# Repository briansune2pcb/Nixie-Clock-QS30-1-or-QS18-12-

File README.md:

# Nixie-Clock-QS30-1-or-QS18-12-

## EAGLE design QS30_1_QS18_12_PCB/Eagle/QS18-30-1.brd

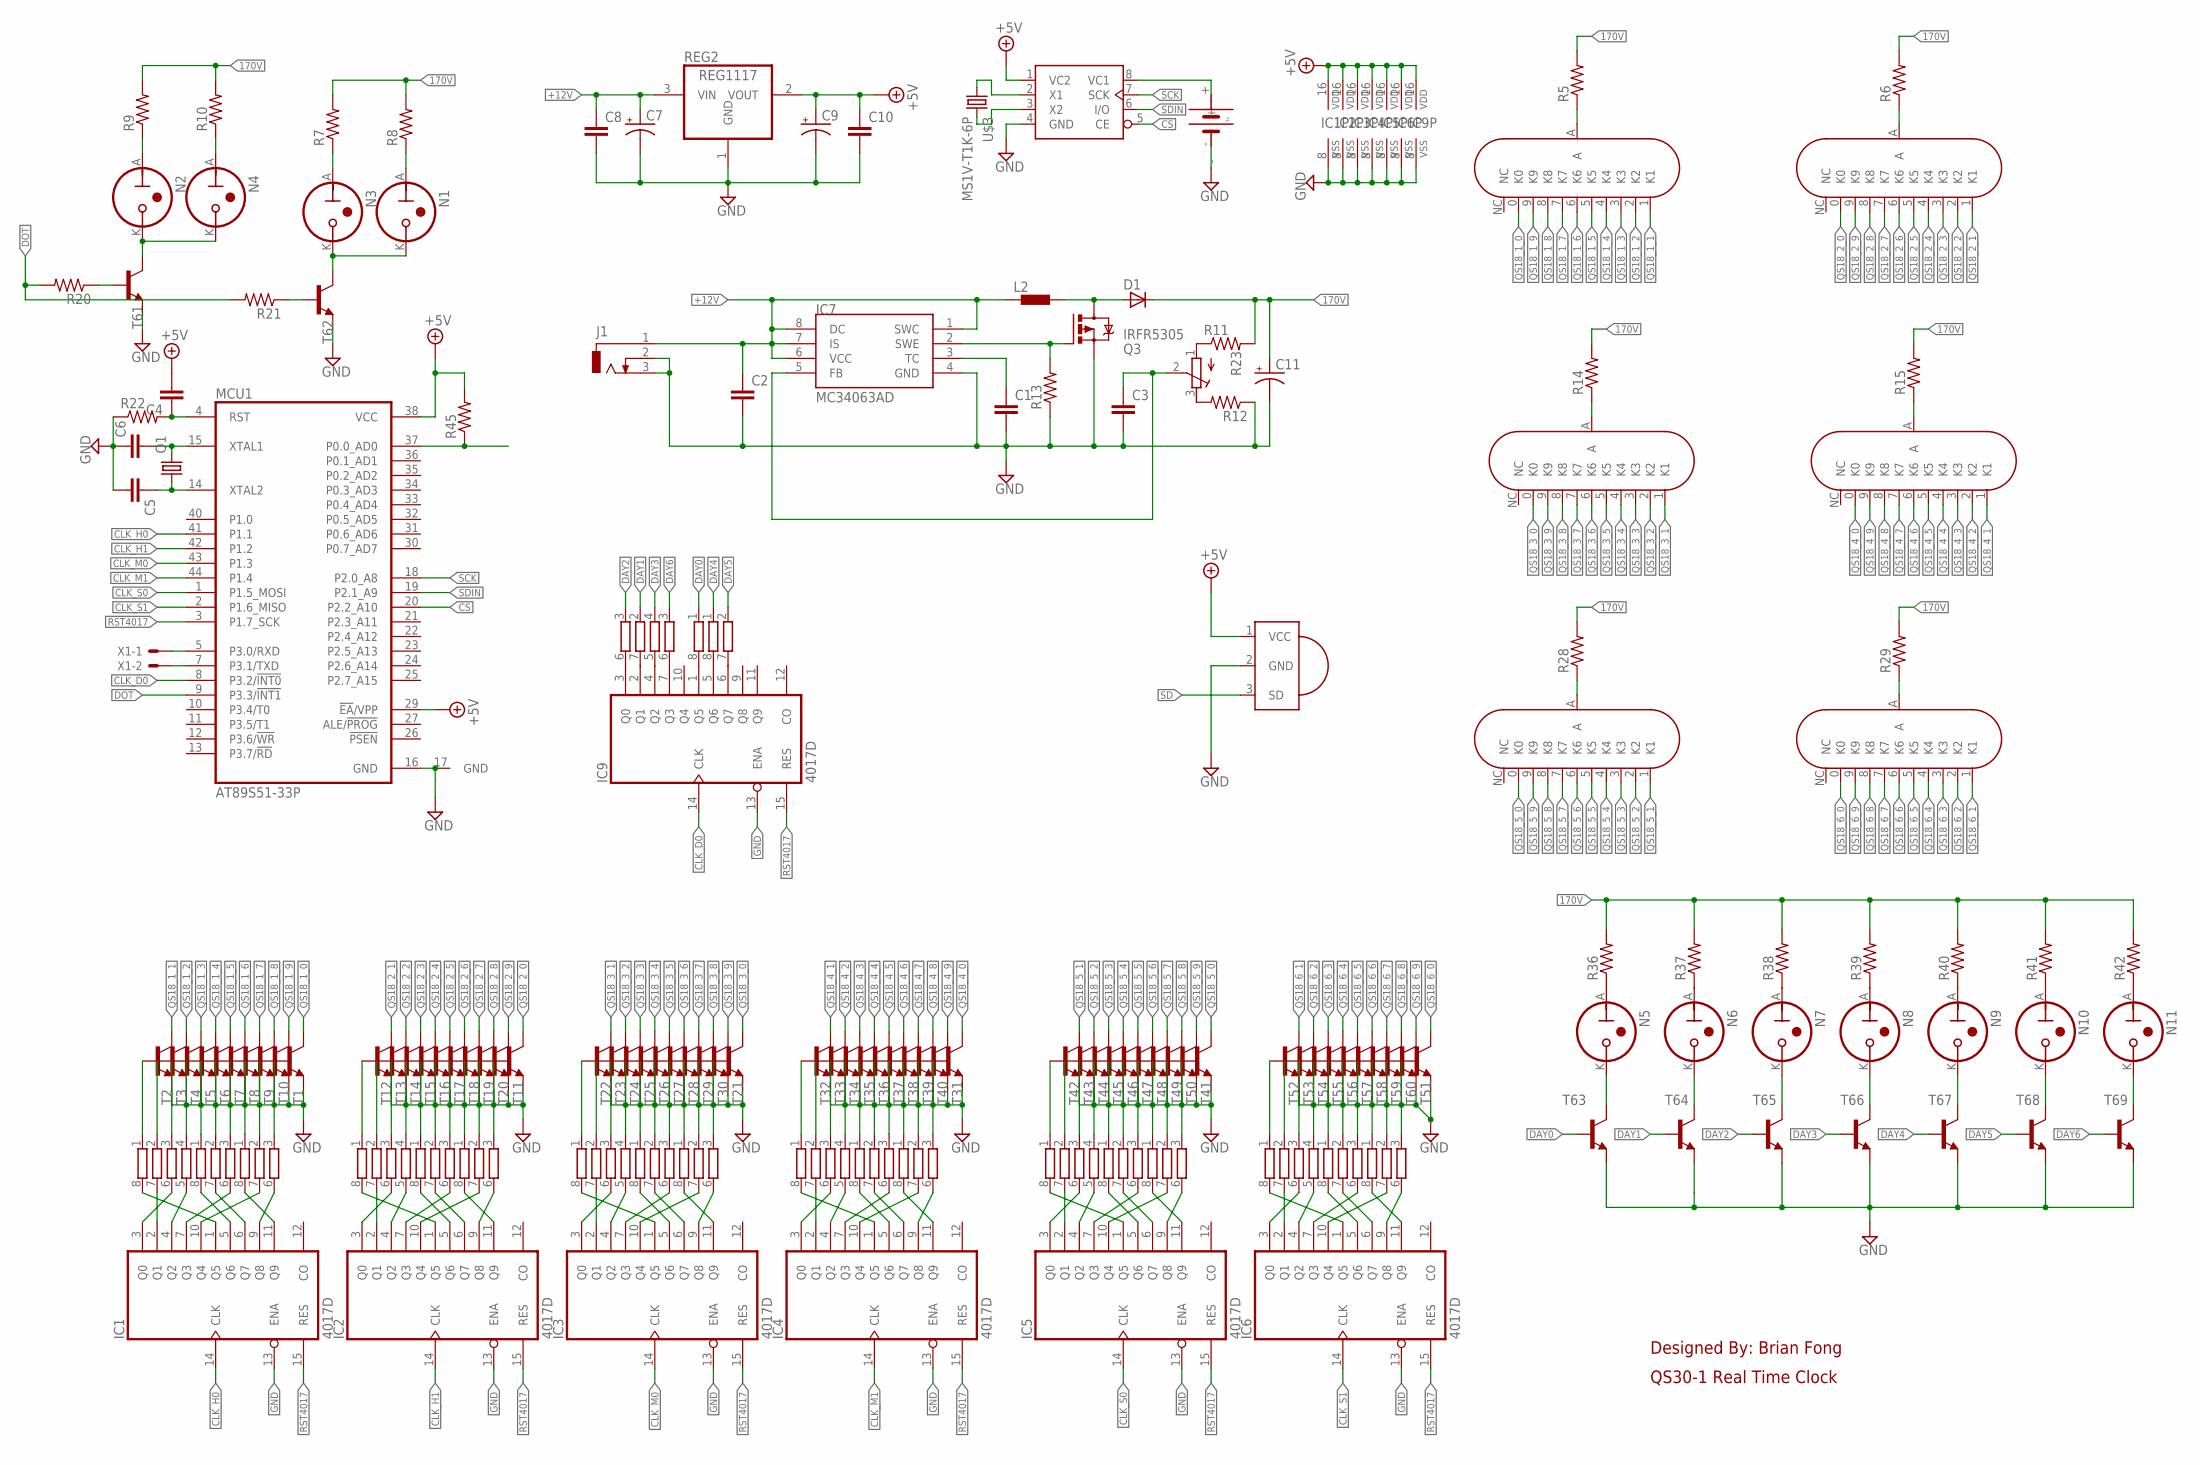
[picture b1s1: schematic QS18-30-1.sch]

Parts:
C1, C2, C3, C5, C6, C8, C10: C-EUC0805; C0805
C4: C-EUC1206; C1206
C7, C9: CPOL-USB/3528-21R; B/3528-21R
C11: CPOL-USG; PANASONIC_G
D1: D-SMB; SMB
IC1, IC2, IC3, IC4, IC5, IC6, IC9: 4017D; SO16
IC7: MC34063AD; SOIC8
J1: DCJ0303
L2: DR10301033; DR1033
MCU1: AT89S51-33P; TQFP44
N1, N2, N3, N4, N5, N6, N7, N8, N9, N10: IN-3
N11: Mon; IN-3
Q1: CRYSTALHC49UP; HC49UP
Q3: IRFR5305; D-PAK_TO252AA
R1, R2, R3, R4, R16, R17, R18, R19, R24, R25, R26, R27, R30, R31, R32, R33, R34, R35, R43, R44: 4R-NEXB38V; EXB38V
R5, R6, R7, R8, R9, R10, R14, R15, R20, R21, R22, R28, R29, R36, R37, R38, R39, R40, R41, R42, R45: R-US_M0805; M0805
R11, R12, R13: R-US_R0805; R0805
R23: R-TRIMM3374; RTRIM3374
REG2: REG1117; SOT223
T1, T2, T3, T4, T5, T6, T7, T8, T9, T10, T11, T12, T13, T14, T15, T16, T17, T18, T19, T20, T21, T22, T23, T24, T25, T26, T27, T28, T29, T30, T31, T32, T33, T34, T35, T36, T37, T38, T39, T40, T41, T42, T43, T44, T45, T46, T47, T48, T49, T50, T51, T52, T53, T54, T55, T56, T57, T58, T59, T60, T61, T62, T63, T64, T65, T66, T67, T68, T69: MMBT5551LT1-NPN-SOT23-BEC; SOT23-BEC
TUBE1, TUBE2, TUBE3, TUBE4, TUBE5, TUBE6: QS30-1R1; QS30-1_V3
U$1: DS1302SOP08; SOP08
U$2: 1220BATTERY_SF; 1220BATTERY
U$3: MS1V-T1K-6P; MS1V-T1K
U$4: HX1838; TO92-
X1: 332-02

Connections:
170V: C11.+, D1.1 (C), R5.2, R6.2, R7.2, R8.2, R9.2, R10.2, R11.2, R14.2, R15.2, R28.2, R29.2, R36.2, R37.2, R38.2, R39.2, R40.2, R41.2, R42.2
+5V: C4.2, C9.+, C10.1, IC1.16 (VDD), IC2.16 (VDD), IC3.16 (VDD), IC4.16 (VDD), IC5.16 (VDD), IC6.16 (VDD), IC9.16 (VDD), MCU1.29 (!EA!/VPP), MCU1.38 (VCC), R45.2, REG2.2 (VOUT), U$1.1 (VC2), U$4.1 (VCC)
+12V: C2.1, C7.+, C8.1, IC7.1 (SWC), IC7.6 (VCC), IC7.7 (IS), IC7.8 (DC), J1.1, L2.1, REG2.3 (VIN)
CLK_D0: IC9.14 (CLK), MCU1.8 (P3.2/!INT0)
CLK_H0: IC1.14 (CLK), MCU1.41 (P1.1)
CLK_H1: IC2.14 (CLK), MCU1.42 (P1.2)
CLK_M0: IC3.14 (CLK), MCU1.43 (P1.3)
CLK_M1: IC4.14 (CLK), MCU1.44 (P1.4)
CLK_S0: IC5.14 (CLK), MCU1.1 (P1.5_MOSI)
CLK_S1: IC6.14 (CLK), MCU1.2 (P1.6_MISO)
CS: MCU1.20 (P2.2_A10), U$1.5 (CE)
DAY0: R43.1, T63.B
DAY1: R43.2 (1), T64.B
DAY2: R43.3 (1), T65.B
DAY3: R43.4 (1), T66.B
DAY4: R44.1, T67.B
DAY5: R44.2 (1), T68.B
DAY6: R44.3 (1), T69.B
DOT: MCU1.9 (P3.3/!INT1), R20.2, R21.2
GND: C1.2, C2.2, C3.2, C5.2, C6.1, C7.-, C8.2, C9.-, C10.2, C11.-, IC1.8 (VSS), IC1.13 (ENA), IC2.8 (VSS), IC2.13 (ENA), IC3.8 (VSS), IC3.13 (ENA), IC4.8 (VSS), IC4.13 (ENA), IC5.8 (VSS), IC5.13 (ENA), IC6.8 (VSS), IC6.13 (ENA), IC7.4 (GND), IC9.8 (VSS), IC9.13 (ENA), J1.2, J1.3, MCU1.16 (GND), MCU1.17 (GND), Q3.3 (S), R12.1, R13.1, R22.1, REG2.1 (GND), T1.E, T2.E, T3.E, T4.E, T5.E, T6.E, T7.E, T8.E, T9.E, T10.E, T11.E, T12.E, T13.E, T14.E, T15.E, T16.E, T17.E, T18.E, T19.E, T20.E, T21.E, T22.E, T23.E, T24.E, T25.E, T26.E, T27.E, T28.E, T29.E, T30.E, T31.E, T32.E, T33.E, T34.E, T35.E, T36.E, T37.E, T38.E, T39.E, T40.E, T41.E, T42.E, T43.E, T44.E, T45.E, T46.E, T47.E, T48.E, T49.E, T50.E, T51.E, T52.E, T53.E, T54.E, T55.E, T56.E, T57.E, T58.E, T59.E, T60.E, T61.E, T62.E, T63.E, T64.E, T65.E, T66.E, T67.E, T68.E, T69.E, U$1.4 (GND), U$2.-, U$4.2 (GND)
unnamed: C5.1, MCU1.14 (XTAL2), Q1.1
unnamed: C6.2, MCU1.15 (XTAL1), Q1.2
unnamed: R1.1, T2.B
unnamed: R1.2 (1), T3.B
unnamed: R1.3 (1), T4.B
unnamed: R4.1, T12.B
unnamed: R1.4 (1), T5.B
unnamed: R2.1, T6.B
unnamed: R2.2 (1), T7.B
unnamed: R2.3 (1), T8.B
unnamed: R3.1, T9.B
unnamed: R3.2 (1), T10.B
unnamed: R3.3 (1), T1.B
unnamed: R4.2 (1), T13.B
unnamed: R4.3 (1), T14.B
unnamed: R4.4 (1), T15.B
unnamed: R16.1, T16.B
unnamed: R16.2 (1), T17.B
unnamed: R16.3 (1), T18.B
unnamed: R17.1, T19.B
unnamed: R17.2 (1), T20.B
unnamed: R17.3 (1), T11.B
unnamed: R14.1, TUBE3.A
unnamed: R15.1, TUBE4.A
unnamed: R5.1, TUBE1.A
unnamed: R18.1, T22.B
unnamed: R6.1, TUBE2.A
unnamed: R18.2 (1), T23.B
unnamed: R18.3 (1), T24.B
unnamed: R18.4 (1), T25.B
unnamed: R19.1, T26.B
unnamed: R19.2 (1), T27.B
unnamed: R19.3 (1), T28.B
unnamed: R24.1, T29.B
unnamed: R24.2 (1), T30.B
unnamed: R24.3 (1), T21.B
unnamed: R25.1, T32.B
unnamed: R25.2 (1), T33.B
unnamed: R25.3 (1), T34.B
unnamed: R25.4 (1), T35.B
unnamed: R26.1, T36.B
unnamed: R26.2 (1), T37.B
unnamed: R26.3 (1), T38.B
unnamed: R27.1, T39.B
unnamed: R27.2 (1), T40.B
unnamed: R27.3 (1), T31.B
unnamed: IC3.1 (Q5), R18.8 (2)
unnamed: IC3.2 (Q1), R18.7 (2)
unnamed: N3.A, R7.1
unnamed: N1.A, R8.1
unnamed: N2.A, R9.1
unnamed: N4.A, R10.1
unnamed: IC7.2 (SWE), Q3.1 (G), R13.2
unnamed: MCU1.5 (P3.0/RXD), X1.1
unnamed: C1.1, IC7.3 (TC)
unnamed: C3.1, IC7.5 (FB), R23.2 (S)
unnamed: D1.2 (A), L2.2, Q3.4 (D)
unnamed: IC3.3 (Q0), R18.6 (2)
unnamed: IC3.4 (Q2), R18.5 (2)
unnamed: IC3.5 (Q6), R19.8 (2)
unnamed: MCU1.7 (P3.1/TXD), X1.2
unnamed: IC3.6 (Q7), R19.7 (2)
unnamed: IC3.7 (Q3), R19.6 (2)
unnamed: IC3.9 (Q8), R24.6 (2)
unnamed: IC3.11 (Q9), R24.8 (2)
unnamed: IC3.10 (Q4), R24.7 (2)
unnamed: IC4.3 (Q0), R25.6 (2)
unnamed: IC4.1 (Q5), R25.8 (2)
unnamed: IC4.2 (Q1), R25.7 (2)
unnamed: IC4.11 (Q9), R27.8 (2)
unnamed: IC4.9 (Q8), R27.6 (2)
unnamed: IC4.10 (Q4), R27.7 (2)
unnamed: IC4.4 (Q2), R25.5 (2)
unnamed: IC4.5 (Q6), R26.8 (2)
unnamed: IC4.6 (Q7), R26.7 (2)
unnamed: IC4.7 (Q3), R26.6 (2)
unnamed: IC1.1 (Q5), R1.8 (2)
unnamed: IC1.2 (Q1), R1.7 (2)
unnamed: IC1.3 (Q0), R1.6 (2)
unnamed: IC1.4 (Q2), R1.5 (2)
unnamed: IC1.5 (Q6), R2.8 (2)
unnamed: IC1.6 (Q7), R2.7 (2)
unnamed: IC1.7 (Q3), R2.6 (2)
unnamed: IC1.11 (Q9), R3.8 (2)
unnamed: IC1.10 (Q4), R3.7 (2)
unnamed: R28.1, TUBE5.A
unnamed: IC1.9 (Q8), R3.6 (2)
unnamed: R29.1, TUBE6.A
unnamed: N2.K, N4.K, T61.C
unnamed: R20.1, T61.B
unnamed: N1.K, N3.K, T62.C
unnamed: R21.1, T62.B
unnamed: IC2.1 (Q5), R4.8 (2)
unnamed: IC2.2 (Q1), R4.7 (2)
unnamed: IC2.3 (Q0), R4.6 (2)
unnamed: IC2.4 (Q2), R4.5 (2)
unnamed: IC2.5 (Q6), R16.8 (2)
unnamed: U$1.8 (VC1), U$2.+
unnamed: IC2.6 (Q7), R16.7 (2)
unnamed: IC2.7 (Q3), R16.6 (2)
unnamed: IC2.11 (Q9), R17.8 (2)
unnamed: IC2.10 (Q4), R17.7 (2)
unnamed: U$1.2 (X1), U$3.P$1 (1)
unnamed: C4.1, MCU1.4 (RST), R22.2
unnamed: U$1.3 (X2), U$3.P$2 (2)
unnamed: IC2.9 (Q8), R17.6 (2)
unnamed: R30.1, T42.B
unnamed: R30.2 (1), T43.B
unnamed: R30.3 (1), T44.B
unnamed: R30.4 (1), T45.B
unnamed: R31.1, T46.B
unnamed: R31.2 (1), T47.B
unnamed: R31.3 (1), T48.B
unnamed: R32.1, T49.B
unnamed: R32.2 (1), T50.B
unnamed: R32.3 (1), T41.B
unnamed: R33.1, T52.B
unnamed: R33.2 (1), T53.B
unnamed: R33.3 (1), T54.B
unnamed: R33.4 (1), T55.B
unnamed: R34.1, T56.B
unnamed: R34.2 (1), T57.B
unnamed: R34.3 (1), T58.B
unnamed: R35.1, T59.B
unnamed: R35.2 (1), T60.B
unnamed: R35.3 (1), T51.B
unnamed: IC5.1 (Q5), R30.8 (2)
unnamed: IC5.2 (Q1), R30.7 (2)
unnamed: IC5.3 (Q0), R30.6 (2)
unnamed: IC5.4 (Q2), R30.5 (2)
unnamed: IC5.5 (Q6), R31.8 (2)
unnamed: IC5.6 (Q7), R31.7 (2)
unnamed: IC5.7 (Q3), R31.6 (2)
unnamed: IC5.9 (Q8), R32.6 (2)
unnamed: IC5.11 (Q9), R32.8 (2)
unnamed: IC5.10 (Q4), R32.7 (2)
unnamed: IC6.3 (Q0), R33.6 (2)
unnamed: IC6.1 (Q5), R33.8 (2)
unnamed: IC6.2 (Q1), R33.7 (2)
unnamed: IC6.11 (Q9), R35.8 (2)
unnamed: IC6.9 (Q8), R35.6 (2)
unnamed: IC6.10 (Q4), R35.7 (2)
unnamed: IC6.4 (Q2), R33.5 (2)
unnamed: IC6.5 (Q6), R34.8 (2)
unnamed: IC6.6 (Q7), R34.7 (2)
unnamed: IC6.7 (Q3), R34.6 (2)
unnamed: N5.K, T63.C
unnamed: N6.K, T64.C
unnamed: N7.K, T65.C
unnamed: N8.K, T66.C
unnamed: N9.K, T67.C
unnamed: N10.K, T68.C
unnamed: N11.K, T69.C
unnamed: N5.A, R36.1
unnamed: N6.A, R37.1
unnamed: N8.A, R39.1
unnamed: N11.A, R42.1
unnamed: N10.A, R41.1
unnamed: N9.A, R40.1
unnamed: N7.A, R38.1
unnamed: R11.1, R23.1 (E)
unnamed: R12.2, R23.3 (A)
unnamed: IC9.1 (Q5), R43.8 (2)
unnamed: IC9.2 (Q1), R43.7 (2)
unnamed: IC9.3 (Q0), R43.6 (2)
unnamed: IC9.4 (Q2), R43.5 (2)
unnamed: IC9.7 (Q3), R44.6 (2)
unnamed: IC9.5 (Q6), R44.8 (2)
unnamed: IC9.6 (Q7), R44.7 (2)
QS18_1_0: T1.C, TUBE1.0 (K0)
QS18_1_1: T2.C, TUBE1.1 (K1)
QS18_1_2: T3.C, TUBE1.2 (K2)
QS18_1_3: T4.C, TUBE1.3 (K3)
QS18_1_4: T5.C, TUBE1.4 (K4)
QS18_1_5: T6.C, TUBE1.5 (K5)
QS18_1_6: T7.C, TUBE1.6 (K6)
QS18_1_7: T8.C, TUBE1.7 (K7)
QS18_1_8: T9.C, TUBE1.8 (K8)
QS18_1_9: T10.C, TUBE1.9 (K9)
QS18_2_0: T11.C, TUBE2.0 (K0)
QS18_2_1: T12.C, TUBE2.1 (K1)
QS18_2_2: T13.C, TUBE2.2 (K2)
QS18_2_3: T14.C, TUBE2.3 (K3)
QS18_2_4: T15.C, TUBE2.4 (K4)
QS18_2_5: T16.C, TUBE2.5 (K5)
QS18_2_6: T17.C, TUBE2.6 (K6)
QS18_2_7: T18.C, TUBE2.7 (K7)
QS18_2_8: T19.C, TUBE2.8 (K8)
QS18_2_9: T20.C, TUBE2.9 (K9)
QS18_3_0: T21.C, TUBE3.0 (K0)
QS18_3_1: T22.C, TUBE3.1 (K1)
QS18_3_2: T23.C, TUBE3.2 (K2)
QS18_3_3: T24.C, TUBE3.3 (K3)
QS18_3_4: T25.C, TUBE3.4 (K4)
QS18_3_5: T26.C, TUBE3.5 (K5)
QS18_3_6: T27.C, TUBE3.6 (K6)
QS18_3_7: T28.C, TUBE3.7 (K7)
QS18_3_8: T29.C, TUBE3.8 (K8)
QS18_3_9: T30.C, TUBE3.9 (K9)
QS18_4_0: T31.C, TUBE4.0 (K0)
QS18_4_1: T32.C, TUBE4.1 (K1)
QS18_4_2: T33.C, TUBE4.2 (K2)
QS18_4_3: T34.C, TUBE4.3 (K3)
QS18_4_4: T35.C, TUBE4.4 (K4)
QS18_4_5: T36.C, TUBE4.5 (K5)
QS18_4_6: T37.C, TUBE4.6 (K6)
QS18_4_7: T38.C, TUBE4.7 (K7)
QS18_4_8: T39.C, TUBE4.8 (K8)
QS18_4_9: T40.C, TUBE4.9 (K9)
QS18_5_0: T41.C, TUBE5.0 (K0)
QS18_5_1: T42.C, TUBE5.1 (K1)
QS18_5_2: T43.C, TUBE5.2 (K2)
QS18_5_3: T44.C, TUBE5.3 (K3)
QS18_5_4: T45.C, TUBE5.4 (K4)
QS18_5_5: T46.C, TUBE5.5 (K5)
QS18_5_6: T47.C, TUBE5.6 (K6)
QS18_5_7: T48.C, TUBE5.7 (K7)
QS18_5_8: T49.C, TUBE5.8 (K8)
QS18_5_9: T50.C, TUBE5.9 (K9)
QS18_6_0: T51.C, TUBE6.0 (K0)
QS18_6_1: T52.C, TUBE6.1 (K1)
QS18_6_2: T53.C, TUBE6.2 (K2)
QS18_6_3: T54.C, TUBE6.3 (K3)
QS18_6_4: T55.C, TUBE6.4 (K4)
QS18_6_5: T56.C, TUBE6.5 (K5)
QS18_6_6: T57.C, TUBE6.6 (K6)
QS18_6_7: T58.C, TUBE6.7 (K7)
QS18_6_8: T59.C, TUBE6.8 (K8)
QS18_6_9: T60.C, TUBE6.9 (K9)
RST4017: IC1.15 (RES), IC2.15 (RES), IC3.15 (RES), IC4.15 (RES), IC5.15 (RES), IC6.15 (RES), IC9.15 (RES), MCU1.3 (P1.7_SCK)
SCK: MCU1.18 (P2.0_A8), U$1.7 (SCK)
SD: MCU1.37 (P0.0_AD0), R45.1, U$4.3 (SD)
SDIN: MCU1.19 (P2.1_A9), U$1.6 (I/O)

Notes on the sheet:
Designed By: Brian Fong
QS30-1 Real Time Clock

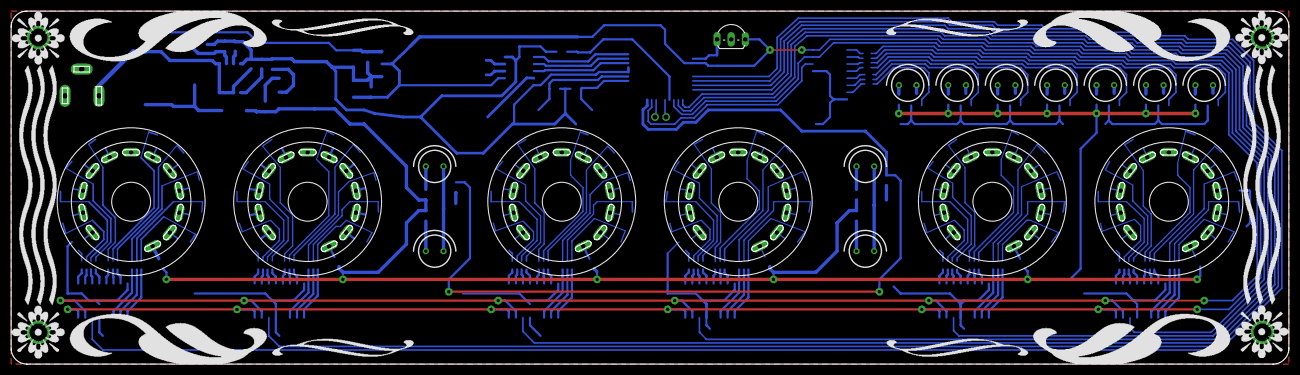
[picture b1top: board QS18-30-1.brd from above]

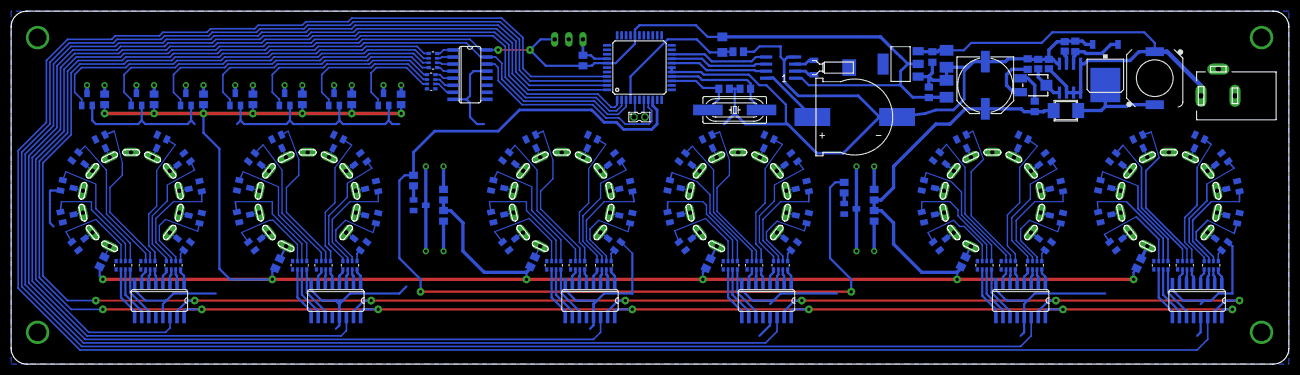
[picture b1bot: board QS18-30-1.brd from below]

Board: 2 copper layers, 229.9 x 63.5 mm, 162 parts (144 on the bottom side), 253 nets.
